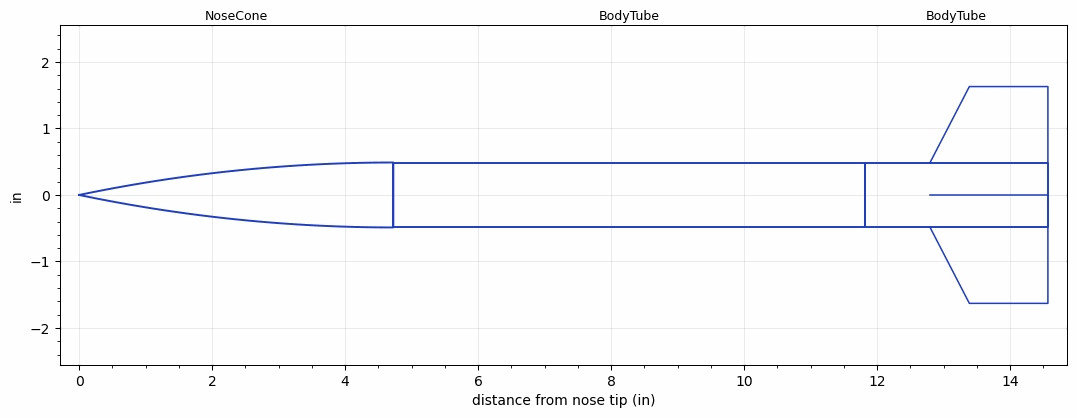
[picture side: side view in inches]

<RASAeroDocument>
 <FileVersion>2</FileVersion>
 <RocketDesign>
  <NoseCone>
   <Length>4.7244</Length>
   <Diameter>0.9764</Diameter>
   <Shape>Tangent Ogive</Shape>
   <Location>0</Location>
  </NoseCone>
  <BodyTube>
   <Length>7.0866</Length>
   <Diameter>0.9764</Diameter>
   <LaunchLugDiameter>0.315</LaunchLugDiameter>
   <LaunchLugLength>0.9842</LaunchLugLength>
   <Location>4.7244</Location>
  </BodyTube>
  <BodyTube>
   <Length>2.7559</Length>
   <Diameter>0.9764</Diameter>
   <Location>11.811</Location>
   <Fin>
    <Count>4</Count>
    <Chord>1.7716</Chord>
    <Span>1.1417</Span>
    <SweepDistance>0.5905</SweepDistance>
    <TipChord>1.1811</TipChord>
    <Thickness>0.0787</Thickness>
    <Location>1.7716</Location>
    <AirfoilSection>Rounded</AirfoilSection>
   </Fin>
  </BodyTube>
  <Surface>Rough Camouflage Paint</Surface>
  <ModifiedBarrowman>False</ModifiedBarrowman>
  <Turbulence>False</Turbulence>
  <UseBooster1>False</UseBooster1>
  <UseBooster2>False</UseBooster2>
 </RocketDesign>
 <LaunchSite>
  <Altitude>0</Altitude>
  <Pressure>29.9214</Pressure>
  <RodAngle>0</RodAngle>
  <RodLength>78.74</RodLength>
  <Temperature>59</Temperature>
  <WindSpeed>4.4739</WindSpeed>
 </LaunchSite>
 <Recovery>
  <Altitude1>0</Altitude1>
  <Altitude2>0</Altitude2>
  <DeviceType1>None</DeviceType1>
  <DeviceType2>None</DeviceType2>
  <Event1>False</Event1>
  <Event2>False</Event2>
  <Size1>0</Size1>
  <Size2>0</Size2>
  <EventType1>None</EventType1>
  <EventType2>None</EventType2>
  <CD1>0</CD1>
  <CD2>0</CD2>
 </Recovery>
 <SimulationList>
  <Simulation>
   <SustainerEngine>A6  (Klima)</SustainerEngine>
   <SustainerLaunchWt>0.1</SustainerLaunchWt>
   <SustainerCG>10.92</SustainerCG>
   <SustainerIgnitionDelay>0</SustainerIgnitionDelay>
   <Booster1SeparationDelay>0</Booster1SeparationDelay>
   <Booster1IgnitionDelay>0</Booster1IgnitionDelay>
   <IncludeBooster1>False</IncludeBooster1>
   <Booster2Delay>0</Booster2Delay>
   <IncludeBooster2>False</IncludeBooster2>
  </Simulation>
 </SimulationList>
</RASAeroDocument>
